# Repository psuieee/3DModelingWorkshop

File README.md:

# 3D Modeling for Electronics Workshop:

In this workshop we will learn some basic techniques to 3D model. The workshop will be showing tips and tricks that are important and useful for when making cases and objects to interact with your electronic projects!

# Requirements:

Charged laptop with a mouse

# Signing up for Autodesk Fusion:

1. Go to [this website](https://www.autodesk.com/products/fusion-360/personal) 
2. Sign up for an account
3. Open the downloaded file and continue through the prompts

# Resources

1. Convert images to svg: [https://www.freeconvert.com/svg-converter](https://www.freeconvert.com/svg-converter)
2. Keychain upload: [https://forms.gle/uBGSUmTg58nGyhP97](https://forms.gle/uBGSUmTg58nGyhP97)

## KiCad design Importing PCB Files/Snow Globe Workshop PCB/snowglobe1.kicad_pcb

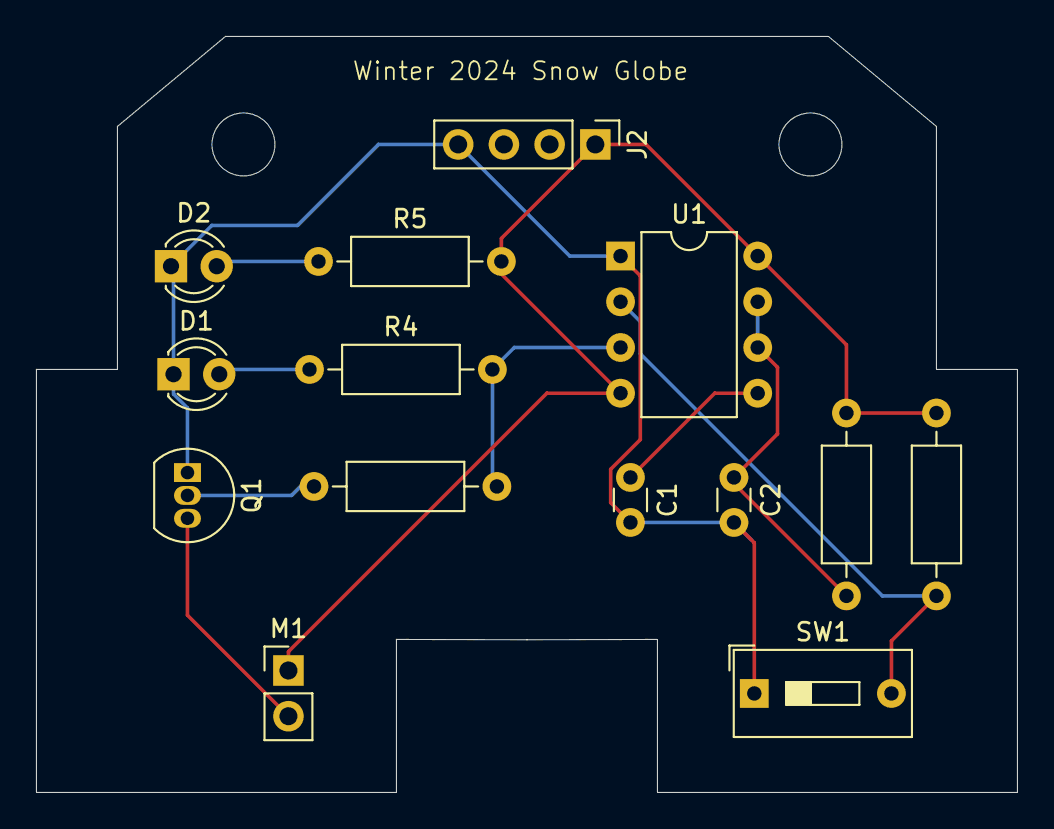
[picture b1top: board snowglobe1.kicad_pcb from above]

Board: 2 copper layers, 54.5 x 42.0 mm, 14 parts (0 on the bottom side), 10 nets.

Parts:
C1: 100nF; C_Disc_D3.0mm_W1.6mm_P2.50mm
C2: 0.47μF; C_Disc_D3.0mm_W1.6mm_P2.50mm
D1: MOTOR_LED; LED_D3.0mm
D2: POWER_LED; LED_D3.0mm
J2: USB_B; PinHeader_1x04_P2.54mm_Vertical
M1: Motor_DC; PinHeader_1x02_P2.54mm_Vertical
Q1: PN2222A; TO-92_Inline
R1, R4, R5: 390Ω; R_Axial_DIN0207_L6.3mm_D2.5mm_P10.16mm_Horizontal
R2: 10MΩ; R_Axial_DIN0207_L6.3mm_D2.5mm_P10.16mm_Horizontal
R3: 10kΩ; R_Axial_DIN0207_L6.3mm_D2.5mm_P10.16mm_Horizontal
SW1: Button_INPUT; SW_DIP_SPSTx01_Slide_9.78x4.72mm_W7.62mm_P2.54mm
U1: NE555P Timer; DIP-8_W7.62mm

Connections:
GND: C1.2, C2.2, D1.1 (K), D2.1 (K), J2.4 (GND), Q1.1 (E), SW1.1, U1.1 (GND)
unnamed: D1.2 (A), R4.1
unnamed: D2.2 (A), R5.1
unnamed: M1.2 (-), Q1.3 (C)
unnamed: Q1.2 (B), R1.2
unnamed: C1.1, U1.5 (CV)
unnamed: C2.1, R2.2, U1.6 (THR), U1.7 (DIS)
unnamed: R1.1, R4.2, U1.3 (Q)
unnamed: R3.2, SW1.2, U1.2 (TR)
VDD: J2.1 (VBUS), M1.1 (+), R2.1, R3.1, R5.2, U1.4 (R), U1.8 (VCC)
